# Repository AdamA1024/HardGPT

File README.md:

# HardGPT

A character-level GPT running entirely on a TI MSPM0G3507 Cortex-M0+ — no host
PC, no network, no accelerator. Press **Generate** and the chip composes
fake-Shakespeare one character at a time on a 16x2 LCD, beeping at the start
and end. Three buttons, three LEDs, an active buzzer, and a dollar's worth of
flash.

The model is a 3-layer transformer (4 heads, 48 embedding dims, block size 48,
65-character vocab) trained on the tiny-shakespeare corpus. Weights are int8
symmetric per-output-channel quantized so the whole network fits in flash, and
the KV cache is also int8 to keep SRAM use sane during generation.

## Repo layout

```
HardGPT/
├── main.c              firmware entry point — UI, transformer inference loop
├── lcd.h               header-only HD44780-via-PCF8574 driver
├── weights.h           int8 weights + vocab, generated by training/export
├── hardgpt.syscfg      sysconfig project: clocks, GPIO, I2C
├── targetConfigs/      CCS debug configs for the launchpad
├── pcb/                kicad project for the board
├── img/                photos used in this readme
└── training/           offline training + weight export pipeline
```

## How it works

The whole firmware lives in a single `main.c` because the model is small
enough that splitting it would just add ceremony. Walking through it top to
bottom:

### Activation and KV-cache buffers

A handful of static SRAM arrays hold the activations of one token at a time:

- `x`, `x_residual`, `x_norm` — the running embedding vector (length `N_EMBD`)
- `qkv` — the combined query/key/value projection (length `3 * N_EMBD`)
- `ffn_hidden` — the 4×-wide MLP hidden state
- `logits` — the output distribution over the 65-character vocabulary
- `x_q` — int8 scratch buffer used whenever we need to quantize an activation

The KV cache is `int8 kv_cache[N_LAYER][BLOCK_SIZE][2 * N_EMBD]` with
`float kv_scales[...]` alongside, so each cached K and V vector keeps its own
quantization scale. Storing it as int8 cuts the cache footprint by ~4× versus
float.

### Math primitives

Everything that touches the hot path uses fast, approximate floats:

- `quantize_vec` — symmetric int8 quantization of a vector with one shared
  scale, used to feed activations into the int8 matmul.
- `matvec_i8i8_pc` — the workhorse. Multiplies an int8 weight matrix (with
  per-row scales) against an int8 activation vector (with one scale) and
  accumulates into int32, then converts to float at the end. This single
  routine handles QKV projection, attention output projection, and both MLP
  matmuls.
- `fast_invsqrt` — the famous Quake `0x5f3759df` trick + one Newton-Raphson
  step. Used by both LayerNorm and the attention scaling factor.
- `fast_expf` — Schraudolph's bit-hack exp. Wildly inaccurate in absolute
  terms but plenty good once softmax normalizes.
- `fast_tanhf` — a Padé approximation, ~1 % error in [-3, 3], used inside
  GELU.
- `layernorm`, `gelu`, `softmax` — built on top of the above.

### The transformer block

`Layer` is just a struct of pointers into `weights.h` so the block code can
work with `L->attn_qkv_w` etc. instead of macro-mangled names.
`init_layers()` wires layer 0/1/2 once at boot.

`block_forward(layer_i, pos)` does one transformer block:

1. Save the residual, layernorm into `x_norm`.
2. Quantize `x_norm`, run the QKV matmul, split into `q`, `k`, `v`.
3. Quantize the new `k` and `v` and store them at `kv_cache[layer_i][pos]`.
4. For each head: dot the head's `q` against every cached `k_t` (dequantizing
   on the fly), scale by `1/sqrt(head_dim)`, softmax, then accumulate the
   weighted sum of cached `v_t`.
5. Quantize the attention output, run the output projection, add the residual.
6. LayerNorm again, run the 4× MLP with GELU, project back, add the residual.

`forward(token_id, pos)` adds the token + position embeddings, calls
`block_forward` for each layer, runs the final LayerNorm, and reuses the
embedding table as the LM head (weight tying) to produce `logits`.

`slide_kv_cache()` shifts the cache left by one when generation runs past
`BLOCK_SIZE`, so the model always sees the most recent `BLOCK_SIZE - 1`
tokens.

### Sampling

Two sampling modes:

- `sample_argmax` — greedy.
- `sample_temp(temperature)` — divide logits by temperature, softmax, draw
  from the distribution using a small linear-congruential RNG.

The probability of the chosen token is stashed in `last_token_prob` so the
"confidence" LED can light up when the model is sure.

### LCD typewriter

`LcdView` holds a 2-row shadow buffer plus the current `(row, col)`. As
characters arrive, `lcd_view_putchar` writes them straight to the LCD and
mirrors them into the shadow buffer. When the cursor walks off row 1, we
copy row 1 up to row 0, blank row 1, and continue — the result is a smooth
typewriter that scrolls upward indefinitely.

### UI / main loop

Boot sequence:

1. `SYSCFG_DL_init()` brings up clocks/GPIO/I2C from sysconfig.
2. `init_layers()` wires the layer pointer table.
3. `lcd_init()` runs the HD44780 wake-up dance and switches it into 4-bit mode.
4. A short buzzer beep confirms power-on.

Then the forever loop:

- **Idle** screen says `HardGPT v1.0 / Press Generate!`. The buttons let you
  cycle through seeds (`Random`, `KING`, `ROMEO`, `LORD`, `HENRY`) or peek at
  the temperature.
- **Generate**: beep, light up the "running" LED, clear the KV cache, print
  the seed name as a cosmetic prefix, then loop:
    - run `forward(token, pos)`
    - sample the next token
    - print it through the LCD typewriter
    - toggle LED 2 (one tick per token), light LED 3 if `last_token_prob > 0.5`
    - increment `pos`; slide the KV cache if we hit `BLOCK_SIZE`
    - bail out early if Generate is pressed again (interrupts the run)
- After 300 tokens (or interrupt), beep twice, wait, and return to idle.

## Hardware

| Peripheral    | Pin                              | Purpose                                                |
|---------------|----------------------------------|--------------------------------------------------------|
| 16x2 LCD      | I2C0 — SDA on PA0, SCL on PA1    | shows generated text, scrolls upward (PCF8574 backpack)|
| Generate btn  | PA5  (input, internal pull-up)   | start / interrupt generation                           |
| Temp btn      | PA7  (input, internal pull-up)   | preview the sampling temperature                       |
| Seed btn      | PA8  (input, internal pull-up)   | cycle the seed character / name                        |
| LED 1         | PA12 (output)                    | "running" — lit during generation                      |
| LED 2         | PA17 (output)                    | toggles once per generated token                       |
| LED 3         | PA18 (output)                    | lit when sampled token's probability > 0.5             |
| Buzzer        | PA22 (output, NPN switch)        | boot beep + start/end-of-generation cue                |
| SWD           | SWCLK on PA20, SWDIO on PA19     | flashing / debug from CCS                              |

Pin assignments live in `hardgpt.syscfg`; the SDK generates `ti_msp_dl_config.{c,h}`
into `Debug/` from it.

## Training

The model is trained offline using a trimmed-down fork of Andrej Karpathy's
[**nanoGPT**](https://github.com/karpathy/nanoGPT). Pretty much all of the
training code (`model.py`, `train.py`, `sample.py`, `configurator.py`, the
data prep scripts, the overall project structure) is his — go give that repo
a star. The training pipeline lives in `training/` and is a UV-managed Python
project.

```
training/
├── pyproject.toml
├── uv.lock
├── nanoGPT/                  Karpathy's nanoGPT (trimmed to what we use)
│   ├── model.py              GPT model definition
│   ├── train.py              training loop
│   ├── sample.py             inference / sampling reference
│   ├── configurator.py
│   ├── config/train_micro.py our tiny config (3 layers, 48 dims, ...)
│   ├── data/shakespeare_char/ tiny-shakespeare, char-level tokenizer
│   ├── out-micro/ckpt.pt     trained checkpoint
│   ├── LICENSE               nanoGPT MIT license
│   └── README.md             upstream nanoGPT README
├── export/
│   ├── export_weights.py     converts ckpt.pt → weights.h
│   └── weights.h             generated header (also copied into the firmware)
└── inference_c/              desktop C reference impl, used to sanity-check
    ├── main.c                  the on-chip math before flashing
    └── weights.h
```

End-to-end flow:

```
training/nanoGPT/data/shakespeare_char/prepare.py
        │
        ▼     (tokenize)
   train.bin / val.bin
        │
        ▼     (uv run python nanoGPT/train.py config/train_micro.py)
training/nanoGPT/out-micro/ckpt.pt
        │
        ▼     (uv run python export/export_weights.py)
training/export/weights.h ── copied to ──▶ HardGPT/weights.h
                                                   │
                                                   ▼  (CCS build + flash)
                                            on-chip generation
```

`config/train_micro.py` sets the architecture used by the firmware
(`n_layer=3`, `n_head=4`, `n_embd=48`, `block_size=48`, dropout 0.2) and
trains for 30k iterations on `shakespeare_char` with the AdamW recipe nanoGPT
ships with.

`export_weights.py` does symmetric int8 per-output-channel quantization of
every weight matrix, keeps LayerNorm gains as float (they're tiny), and emits
a single `weights.h` containing:

- the architecture `#define`s (`VOCAB_SIZE`, `N_LAYER`, `N_HEAD`, `N_EMBD`,
  `HEAD_DIM`, `BLOCK_SIZE`)
- the character `vocab[]` lookup table
- token / position embeddings + per-row scales
- per-layer attention QKV, attention proj, MLP fc, MLP proj weights and scales
- per-layer LayerNorm gains as float
- the final LayerNorm gain

That header is exactly what `main.c` `#include`s. The on-chip int8 matmul in
`matvec_i8i8_pc` is the dequantization counterpart to what
`export_weights.py` does at quantization time.

### Reproducing

```bash
cd training
uv sync                                       # install torch, numpy, etc.
uv run python nanoGPT/data/shakespeare_char/prepare.py
uv run python nanoGPT/train.py config/train_micro.py
uv run python export/export_weights.py
cp export/weights.h ../weights.h              # firmware picks it up on next build
```

Then build the firmware in CCS (`Project → Clean → Build`) and flash to the
LP-MSPM0G3507.

## Credits

- **Andrej Karpathy** — the entire training stack (`nanoGPT`) is his work,
  used here under its MIT license. See `training/nanoGPT/LICENSE`.
- Tiny-Shakespeare corpus from char-rnn, also via nanoGPT.
- HardGPT firmware (`main.c`, `lcd.h`, `weights.h` packaging, sysconfig, board
  bring-up) is original to this project.

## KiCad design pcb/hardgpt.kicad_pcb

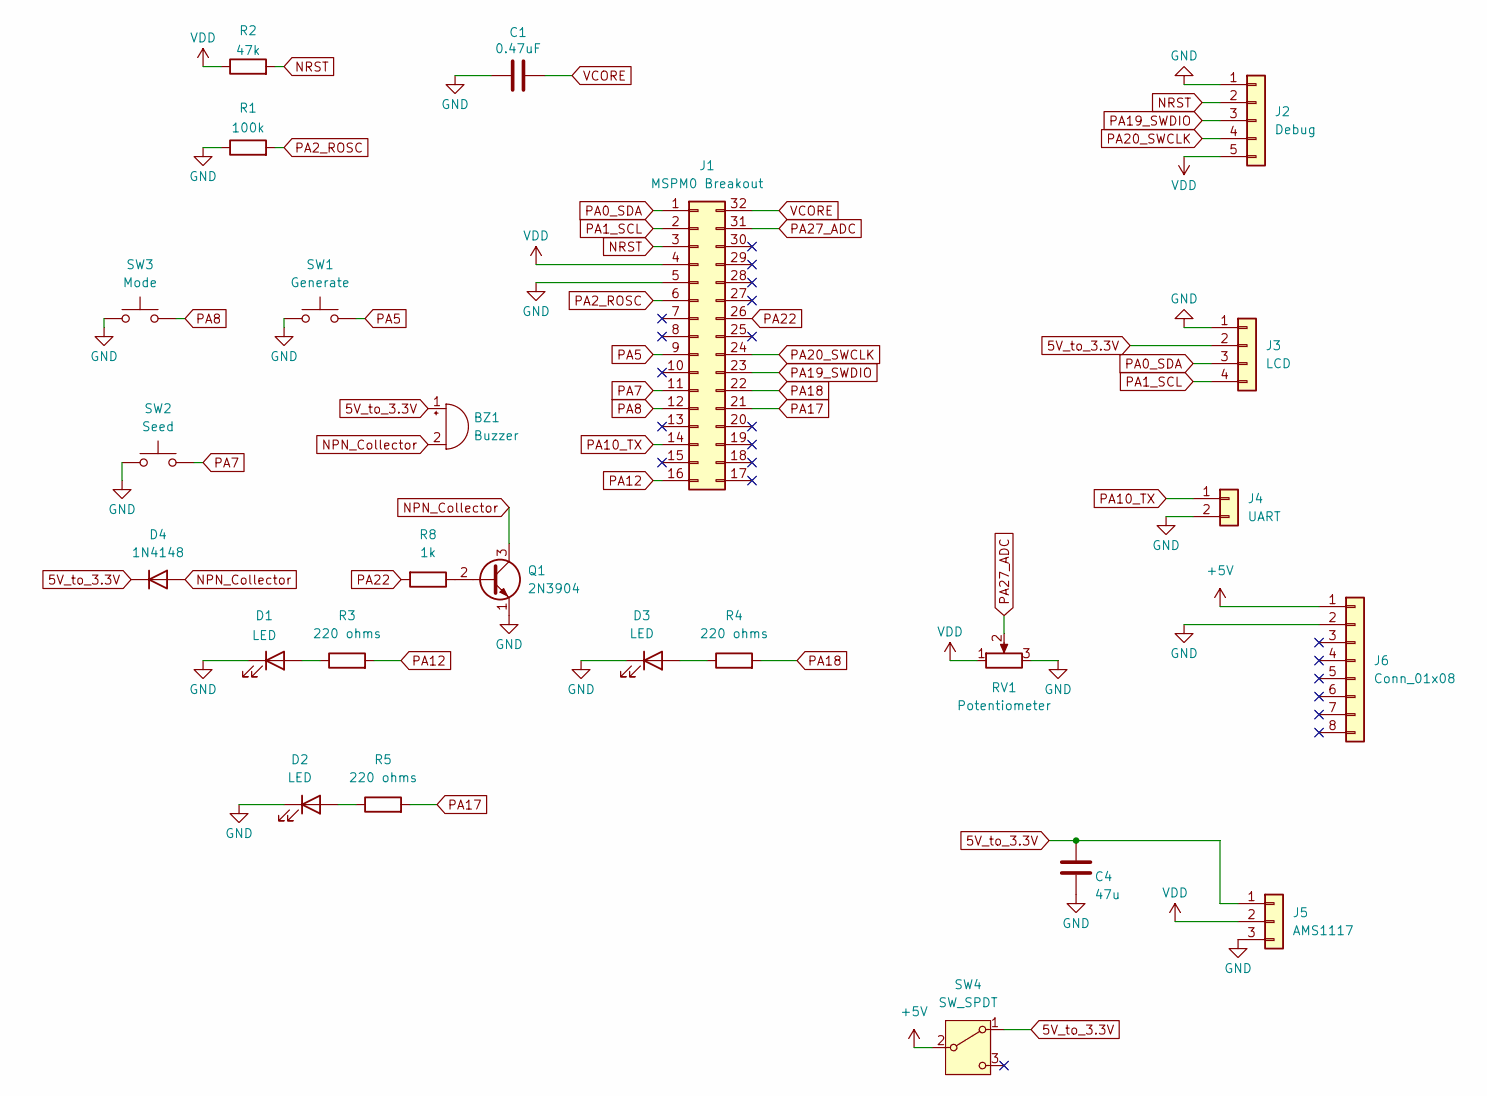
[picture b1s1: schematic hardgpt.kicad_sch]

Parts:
BZ1: Buzzer; Buzzer_TDK_PS1240P02BT_D12.2mm_H6.5mm
C1: 0.47uF; CP_Radial_D5.0mm_P2.00mm
C4: 47u; CP_Radial_D5.0mm_P2.00mm
D1, D2, D3: LED; LED_D3.0mm
D4: 1N4148; D_DO-35_SOD27_P7.62mm_Horizontal
J1: MSPM0 Breakout; DIP-32_W15.24mm_Socket
J2: Debug; PinHeader_1x05_P2.54mm_Vertical
J3: LCD; PinHeader_1x04_P2.54mm_Vertical
J4: UART; PinHeader_1x02_P2.54mm_Vertical
J5: AMS1117; PinHeader_1x03_P2.54mm_Vertical
J6: Conn_01x08; PinHeader_1x08_P2.54mm_Vertical
Q1: 2N3904; TO-92_Inline_Wide
R1: 100k
R2: 47k
R3, R4, R5: 220 ohms; R_Axial_DIN0207_L6.3mm_D2.5mm_P7.62mm_Horizontal
R8: 1k; R_Axial_DIN0207_L6.3mm_D2.5mm_P7.62mm_Horizontal
RV1: Potentiometer; Potentiometer_Alpha_RD901F-40-00D_Single_Vertical
SW1: Generate; SW_PUSH_6mm
SW2: Seed; SW_PUSH_6mm
SW3: Mode; SW_PUSH_6mm
SW4: SW_SPDT; SW_Slide-03_Wuerth-WS-SLTV_10x2.5x6.4_P2.54mm

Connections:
5V_to_3.3V: BZ1.1 (+), C4.2, D4.1 (K), J3.2, J5.1, SW4.1 (A)
+5V: J6.1, SW4.2 (B)
GND: C1.1, C4.1, D1.1 (K), D2.1 (K), D3.1 (K), J1.5 (GND), J2.1, J3.1, J4.2, J5.3, J6.2, Q1.1 (E), R1.1, RV1.3, SW1.1, SW2.1, SW3.1; also elsewhere on the board
NPN_Collector: BZ1.2 (-), D4.2 (A), Q1.3 (C)
NRST: J1.3 (NRST), J2.2, R2.2
unnamed: D1.2 (A), R3.1
unnamed: D2.2 (A), R5.1
unnamed: D3.2 (A), R4.1
unnamed: Q1.2 (B), R8.1
PA0_SDA: J1.1 (PA0), J3.3
PA1_SCL: J1.2 (PA1), J3.4
PA2_ROSC: J1.6 (PA2), R1.2
PA5: J1.9 (PA5), SW1.2
PA7: J1.11 (PA7), SW2.2
PA8: J1.12 (PA8), SW3.2
PA10_TX: J1.14 (PA10_TX), J4.1
PA12: J1.16 (PA12), R3.2
PA17: J1.21 (PA17), R5.2
PA18: J1.22 (PA18), R4.2
PA19_SWDIO: J1.23 (PA19_SWDIO), J2.3
PA20_SWCLK: J1.24 (PA20_SWCLK), J2.4
PA22: J1.26 (PA22), R8.2
PA27_ADC: J1.31 (PA27), RV1.2
VCORE: C1.2, J1.32 (VCORE)
VDD: J1.4 (VDD), J2.5, J5.2, R2.1, RV1.1; also elsewhere on the board

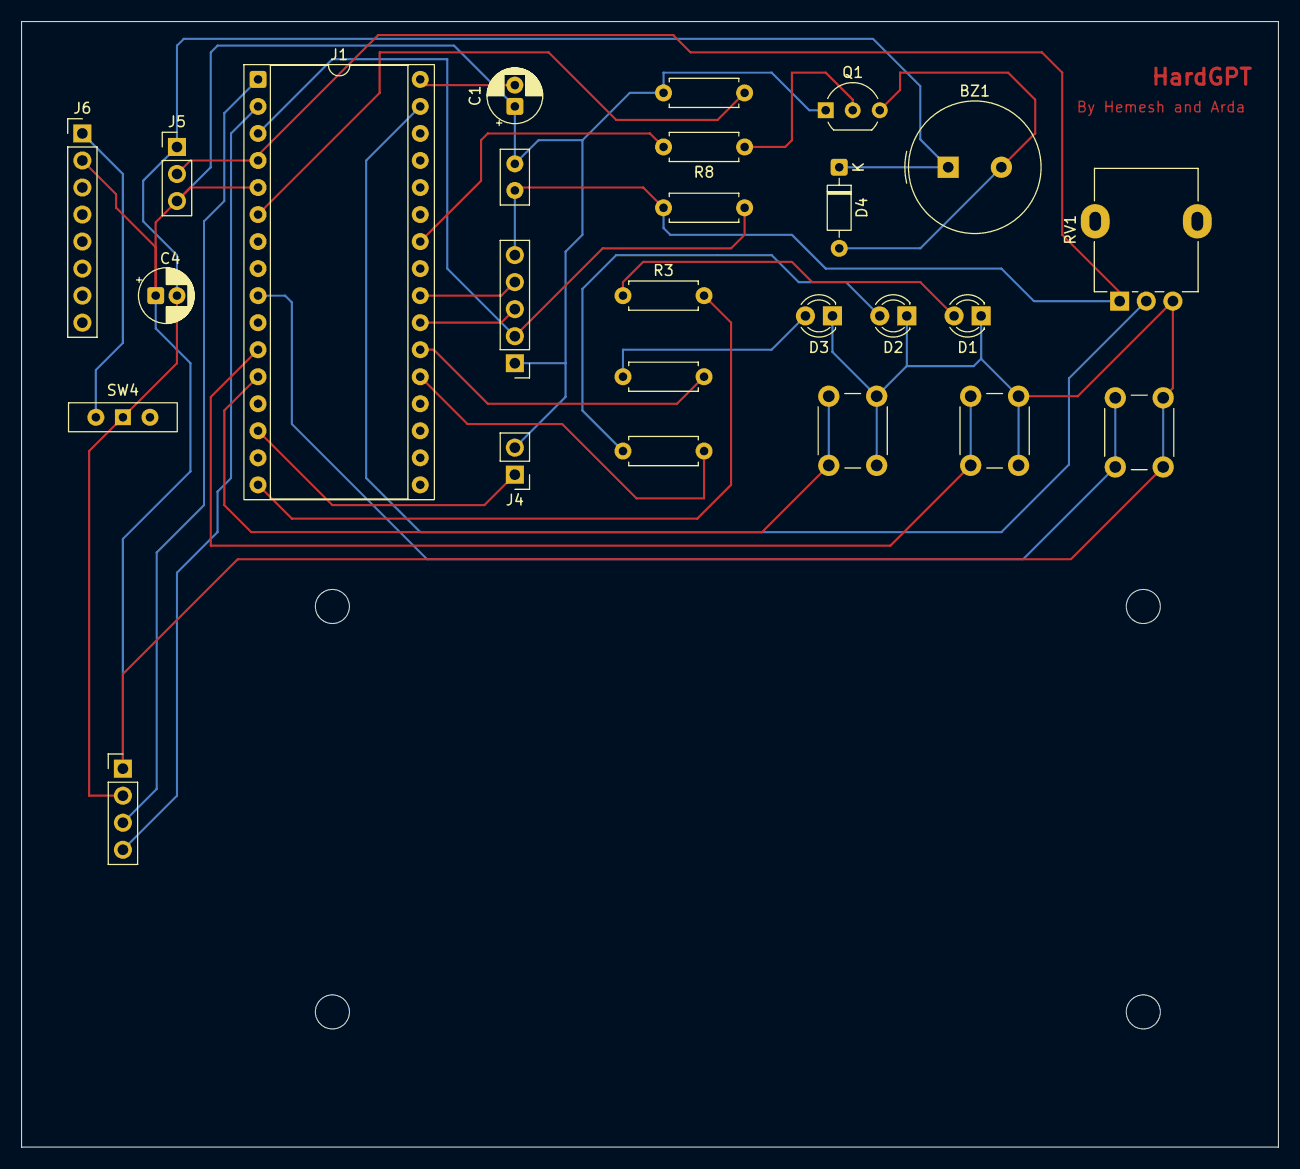
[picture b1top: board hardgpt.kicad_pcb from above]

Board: 2 copper layers, 118.1 x 105.8 mm, 26 parts (0 on the bottom side), 25 nets.

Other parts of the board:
C2: 0.1uF; C_Disc_D5.0mm_W2.5mm_P2.50mm

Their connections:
GND: C2.2; also elsewhere on the board
VDD: C2.1; also elsewhere on the board

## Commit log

2026-05-02 initial commit
    hardgpt firmware and training pipeline. mspm0g3507 character-level
    transformer with int8-quantized weights, kv cache, and a minimal lcd,
    button, led, and buzzer ui. training pipeline is a trimmed fork of
    karpathy's nanogpt plus an int8 weight exporter.
2026-05-02 add pcb design
    kicad project for the hardgpt board, plus rendered top and bottom
    previews. dropped autobackups, drc reports, and the footprint info
    cache from the upstream folder dump.
2026-05-02 add etched pcb and film photos to readme
2026-05-02 tweak readme
2026-05-02 move images below intro
2026-05-02 reorder readme and document pcb in repo layout
2026-05-07 wedding corpus, tokenizer, training config
2026-05-07 scaled down architecture, added eos tokens
